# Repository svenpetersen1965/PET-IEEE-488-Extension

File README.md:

# PET-IEEE-488-Extension
This is a splitter and cable adapter for the Commodore PET IEEE-488 edge connector port. It can serve for connecting a "cheap" standard IEEE-488 cable with both sides IEEE-488 connectors to the edge connector IEEE-488 port of the PET. The original cables with an edge connector are a fortune nowadays.

Also, it can serve as a splitter for the SD2PET future. 

There is a 3D printed case with label for the adapter. 

For splitting the bus, there is a riser card, which attaches to both, the normal and the centronics base board.

Here is a close up of the configuration with the riser card and the SD2PET.

In this configuration, only the bottom part of the case is installed.

This is the base board with an edge connector:

Serving as an easy adapter for a DIY ribbon cable.

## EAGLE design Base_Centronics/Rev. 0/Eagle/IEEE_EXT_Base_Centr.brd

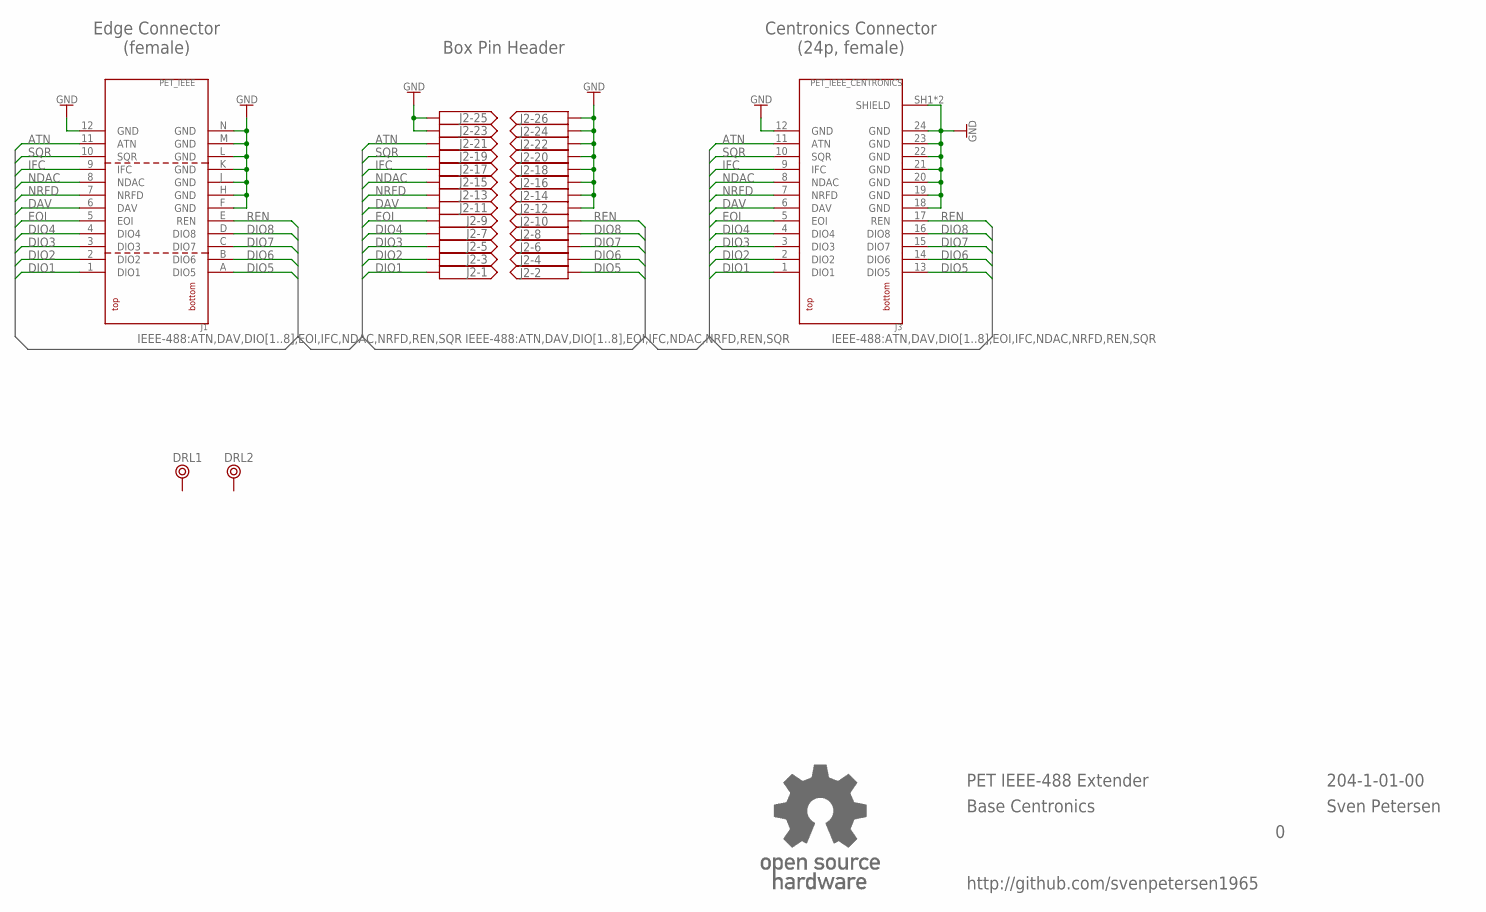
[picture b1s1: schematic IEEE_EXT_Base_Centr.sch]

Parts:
DRL1, DRL2: BOHR3,5
J1: PET_IEEE; USERPORT
J2: 2X13WANNE; 2X13WV
J3: PET_IEEE_CENTRONICS; CENTRONICS24
U$9: OPEN_SOURCE_HW; OPENHW

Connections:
ATN: J1.11 (ATN), J2.21, J3.11 (ATN)
DAV: J1.6 (DAV), J2.11, J3.6 (DAV)
DIO1: J1.1 (DIO1), J2.1, J3.1 (DIO1)
DIO2: J1.2 (DIO2), J2.3, J3.2 (DIO2)
DIO3: J1.3 (DIO3), J2.5, J3.3 (DIO3)
DIO4: J1.4 (DIO4), J2.7, J3.4 (DIO4)
DIO5: J1.A (DIO5), J2.2, J3.13 (DIO5)
DIO6: J1.B (DIO6), J2.4, J3.14 (DIO6)
DIO7: J1.C (DIO7), J2.6, J3.15 (DIO7)
DIO8: J1.D (DIO8), J2.8, J3.16 (DIO8)
EOI: J1.5 (EOI), J2.9, J3.5 (EOI)
GND: J1.12 (GND), J1.F (GND), J1.H (GND), J1.J (GND), J1.K (GND), J1.L (GND), J1.M (GND), J1.N (GND), J2.12, J2.14, J2.16, J2.18, J2.20, J2.22, J2.23, J2.24, J2.25, J2.26, J3.12 (GND), J3.18 (GND), J3.19 (GND), J3.20 (GND), J3.21 (GND), J3.22 (GND), J3.23 (GND), J3.24 (GND), J3.SH1 (SHIELD), J3.SH2 (SHIELD)
IFC: J1.9 (IFC), J2.17, J3.9 (IFC)
NDAC: J1.8 (NDAC), J2.15, J3.8 (NDAC)
NRFD: J1.7 (NRFD), J2.13, J3.7 (NRFD)
REN: J1.E (REN), J2.10, J3.17 (REN)
SQR: J1.10 (SQR), J2.19, J3.10 (SQR)

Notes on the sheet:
PET IEEE-488 Extender
204-1-01-00
Sven Petersen
http://github.com/svenpetersen1965
Base Centronics
Edge Connector (female)
Centronics Connector (24p, female)
Box Pin Header

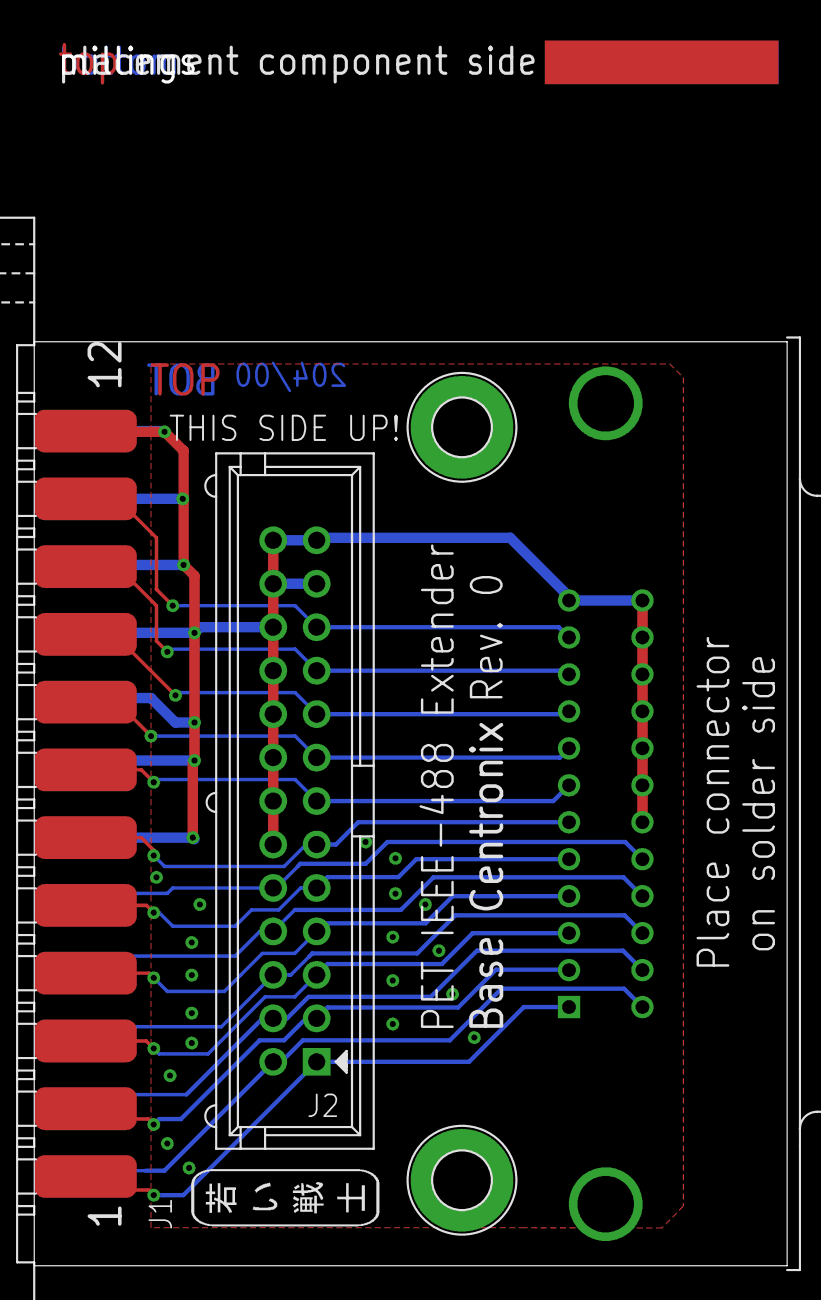
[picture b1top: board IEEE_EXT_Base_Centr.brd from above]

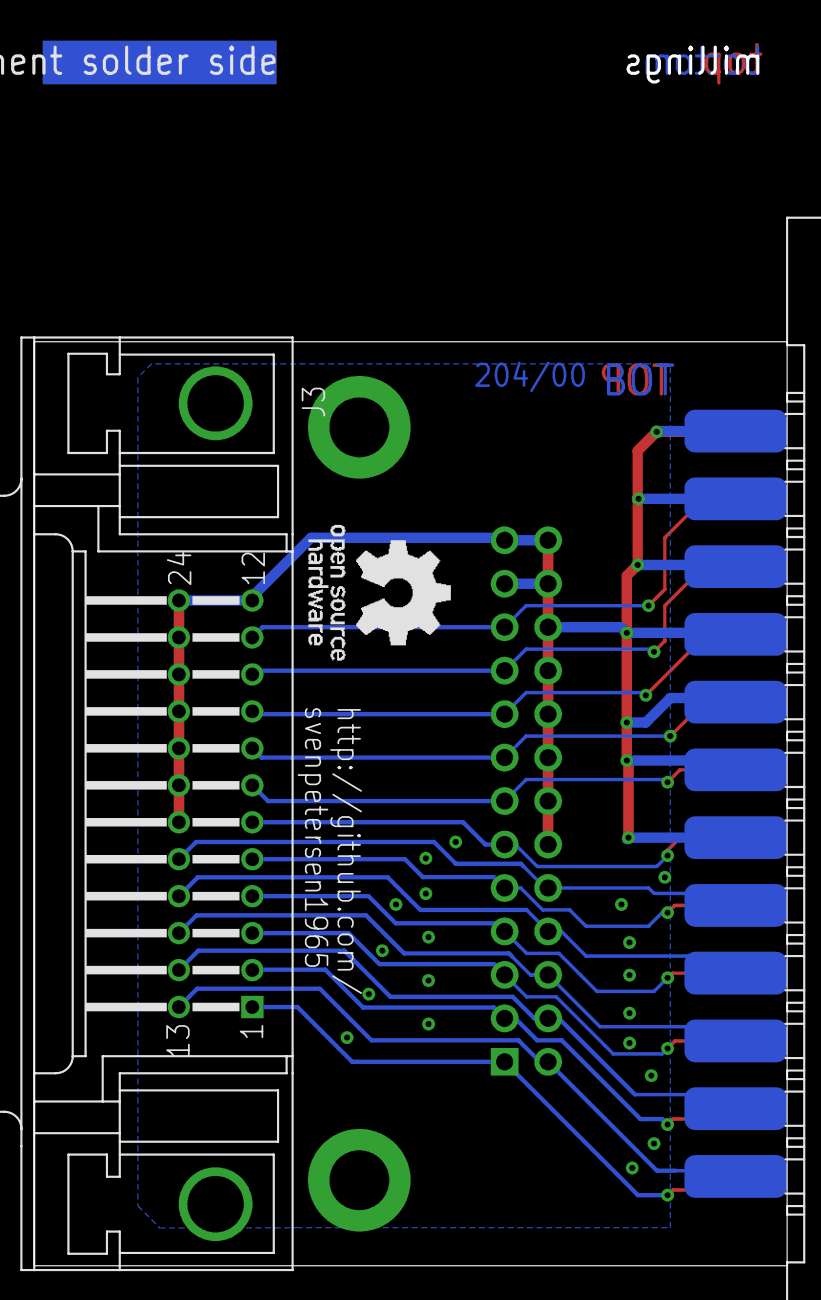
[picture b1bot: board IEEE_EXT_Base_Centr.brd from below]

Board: 2 copper layers, 44.0 x 54.0 mm, 9 parts (2 on the bottom side), 17 nets.

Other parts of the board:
U$8: PCB-TITLE/
U$10: 2LAYER
U$11: SVEN_TAG

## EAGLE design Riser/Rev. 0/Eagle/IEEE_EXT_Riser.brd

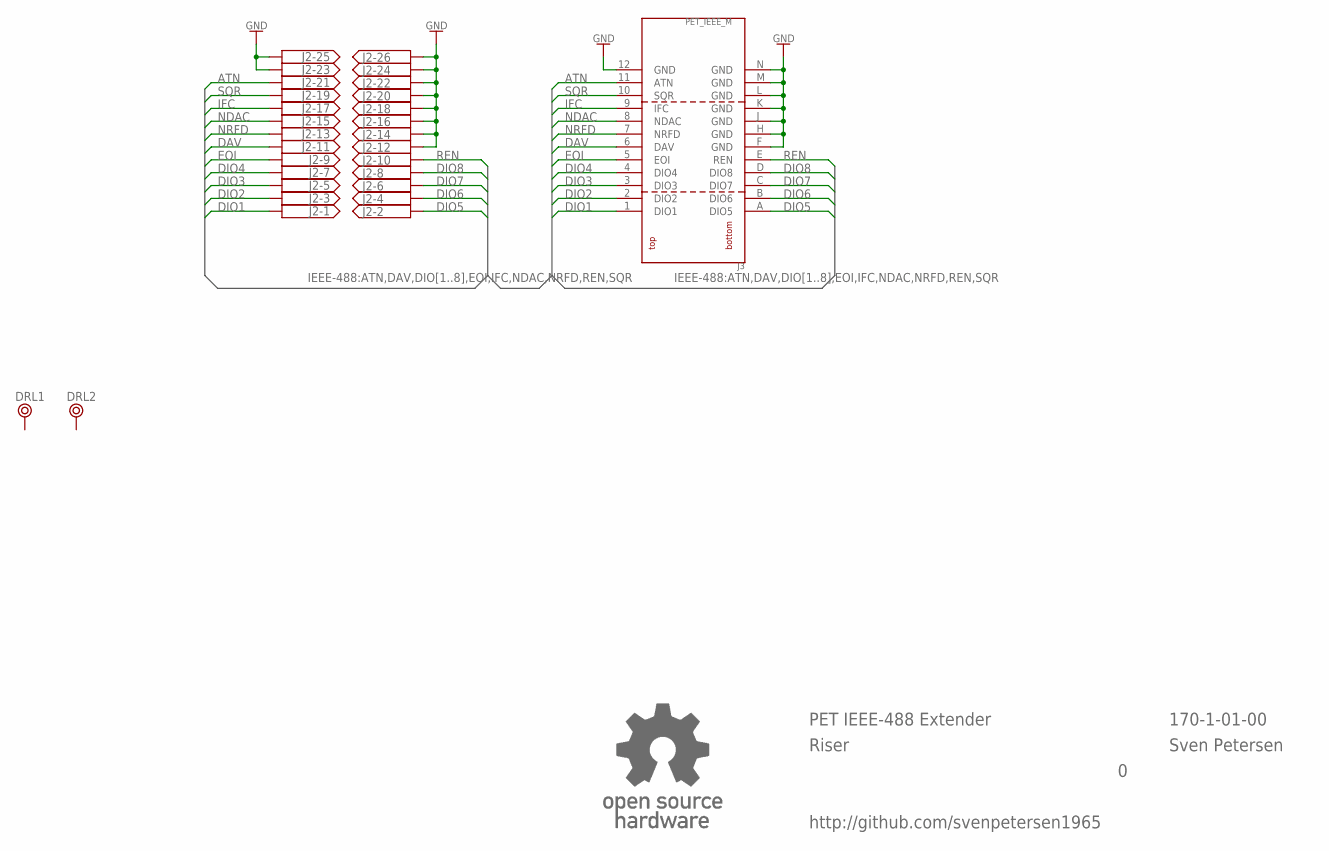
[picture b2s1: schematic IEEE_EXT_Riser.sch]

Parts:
DRL1, DRL2: BOHR3,5
J2: 2X13WANNE; 2X13WV
J3: PET_IEEE_M
U$9: OPEN_SOURCE_HW; OPENHW

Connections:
ATN: J2.21, J3.11 (ATN)
DAV: J2.11, J3.6 (DAV)
DIO1: J2.1, J3.1 (DIO1)
DIO2: J2.3, J3.2 (DIO2)
DIO3: J2.5, J3.3 (DIO3)
DIO4: J2.7, J3.4 (DIO4)
DIO5: J2.2, J3.A (DIO5)
DIO6: J2.4, J3.B (DIO6)
DIO7: J2.6, J3.C (DIO7)
DIO8: J2.8, J3.D (DIO8)
EOI: J2.9, J3.5 (EOI)
GND: J2.12, J2.14, J2.16, J2.18, J2.20, J2.22, J2.23, J2.24, J2.25, J2.26, J3.12 (GND), J3.F (GND), J3.H (GND), J3.J (GND), J3.K (GND), J3.L (GND), J3.M (GND), J3.N (GND)
IFC: J2.17, J3.9 (IFC)
NDAC: J2.15, J3.8 (NDAC)
NRFD: J2.13, J3.7 (NRFD)
REN: J2.10, J3.E (REN)
SQR: J2.19, J3.10 (SQR)

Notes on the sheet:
PET IEEE-488 Extender
170-1-01-00
Sven Petersen
http://github.com/svenpetersen1965
Riser

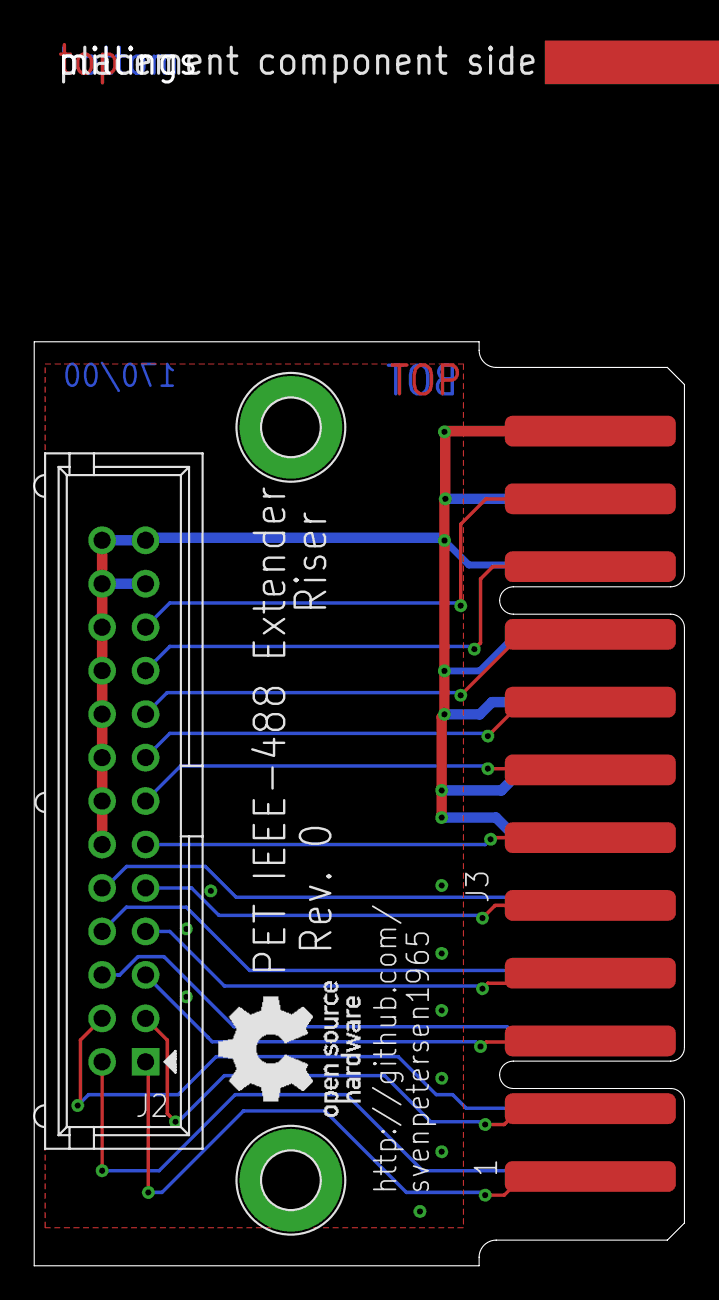
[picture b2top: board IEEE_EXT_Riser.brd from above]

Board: 2 copper layers, 38.0 x 54.0 mm, 7 parts (0 on the bottom side), 17 nets.

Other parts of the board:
U$8: PCB-TITLE/
U$10: 2LAYER
